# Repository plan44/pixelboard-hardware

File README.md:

# Pixelboard Hardware

The **Pixelboard** is a 80*40cm lounge table board only 24mm thick, integrating a 10x20 color pixel matrix, 8 touch keys, a linux controller with WiFi and ethernet and even a power supply. All disguised under a dark plexiglass, looking like a regular lounge table until touched...

With the current software (see [pixelboardd](https://github.com/plan44/pixelboardd) and [pixelboard-config in plan44-feed](https://github.com/plan44/plan44-feed/tree/for-lede-master/pixelboard-config)) you can play tetris (alone or 2 players each on one end of the board), watch Conway's game of life, let text messages scroll over the surface and display small 10x20 pixel PNG images (via web interface).

The board itself is made of 5 layers of lasered plywood and plexiglass. The construction plan is a [Affinity Designer](https://affinity.serif.com/en-us/designer/) drawing in `mechanics/` and there are SVG exports of the layers in `mechanics/exported SVGs for laser/`.

The pixels are made of 33mm spaced WS2813 LED strips, arranged in a 10*20 matrix, all power and data lines connected by two narrow PCBs (see KiCAD files in `electronics/connectorboard`, PCBs can be [ordered here](https://oshpark.com/shared_projects/2NEbDGZJ)). The board is designed such that it works for both sides of the matrix (flipped over at the far end).

The control board is built around a [Onion Omega2](https://onion.io/omega2/), a MediaTek MT7688 based MIPS board with built-in WiFi, 64MB RAM and 16MB Flash, running a LEDE/OpenWRT Linux based firmware (see [here](https://github.com/plan44/plan44-feed/blob/for-lede-master/pixelboard-config/README.md) for how to build the firmware from scratch). The KiCAD files are in `electronics/controlboard`, PCBs can be [ordered here](https://oshpark.com/shared_projects/cvgoJ8vJ)).

The two identical touch key boards are based on the AT42QT1070 chip for handling the touch detection plus a i2c port extender for connecting the indicator LEDs placed in the middle under each touch key. The KiCAD files are in `electronics/touchboard`, PCBs can be [ordered here](https://oshpark.com/shared_projects/GfQ63cgI)).

And in `photos` there are a few images showing various states of assembling all this:

Front glass removed

Controlboard side, just base plate and first lasered frame (lower carrier) keeping the LED matrix, cables, and controlboard in place.

Power supply side, base plate and lower carrier.

Power supply side, now with all plywood layers and touchboard mounted.

Controlboard side, all plywood layers mounted, diffusor plexi sqares inserted, touchboard mounted. Note that this photo does not yet show the hole for a little speaker connected to the MAX98357A i2s amp (but the plan drawings have it).

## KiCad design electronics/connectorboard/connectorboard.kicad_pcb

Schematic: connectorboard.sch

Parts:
C1, C2, C3, C4: 100nF; C_Rect_L7_W2.5_P5
CN1, CN3, CN5, CN7, CN9, CN12, CN14, CN16, CN18, CN20: WS2813-CONN-IN; plan44-WS2813-CONN
CN2, CN4, CN6, CN8, CN10, CN11, CN13, CN15, CN17, CN19: WS2813-CONN-OUT; plan44-WS2813-CONN
J1: STELVIO-2P-508; plan44-STELVIO-2P-508
P1: CONN_01X04; Pin_Header_Straight_1x04

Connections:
+5V: C1.1, C2.1, C3.1, C4.1, CN1.1 (+5V), CN2.4, CN3.1 (+5V), CN4.4, CN5.1 (+5V), CN6.4, CN7.1 (+5V), CN8.4, CN9.1 (+5V), CN10.4, CN11.4, CN12.1 (+5V), CN13.4, CN14.1 (+5V), CN15.4, CN16.1 (+5V), CN17.4, CN18.1 (+5V), CN19.4, CN20.1 (+5V), J1.2, P1.4
GND: C1.2, C2.2, C3.2, C4.2, CN1.4 (GND), CN2.1, CN3.4 (GND), CN4.1, CN5.4 (GND), CN6.1, CN7.4 (GND), CN8.1, CN9.4 (GND), CN10.1, CN11.1, CN12.4 (GND), CN13.1, CN14.4 (GND), CN15.1, CN16.4 (GND), CN17.1, CN18.4 (GND), CN19.1, CN20.4 (GND), J1.1, P1.1, P1.3
unnamed: CN1.2 (DI), P1.2
unnamed: CN2.2, CN3.3 (BI)
unnamed: CN2.3, CN3.2 (DI)
unnamed: CN4.2, CN5.3 (BI)
unnamed: CN4.3, CN5.2 (DI)
unnamed: CN6.2, CN7.3 (BI)
unnamed: CN6.3, CN7.2 (DI)
unnamed: CN8.2, CN9.3 (BI)
unnamed: CN8.3, CN9.2 (DI)
unnamed: CN11.2, CN12.3 (BI)
unnamed: CN11.3, CN12.2 (DI)
unnamed: CN13.2, CN14.3 (BI)
unnamed: CN13.3, CN14.2 (DI)
unnamed: CN15.2, CN16.3 (BI)
unnamed: CN15.3, CN16.2 (DI)
unnamed: CN17.2, CN18.3 (BI)
unnamed: CN17.3, CN18.2 (DI)
unnamed: CN19.2, CN20.3 (BI)
unnamed: CN19.3, CN20.2 (DI)

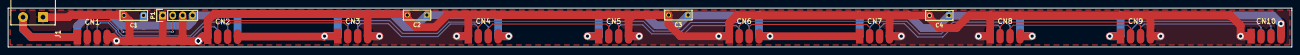
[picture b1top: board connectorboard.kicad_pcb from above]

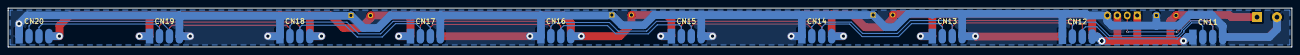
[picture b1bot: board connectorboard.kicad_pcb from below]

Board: 2 copper layers, 327.7 x 9.9 mm, 26 parts (10 on the bottom side), 21 nets.

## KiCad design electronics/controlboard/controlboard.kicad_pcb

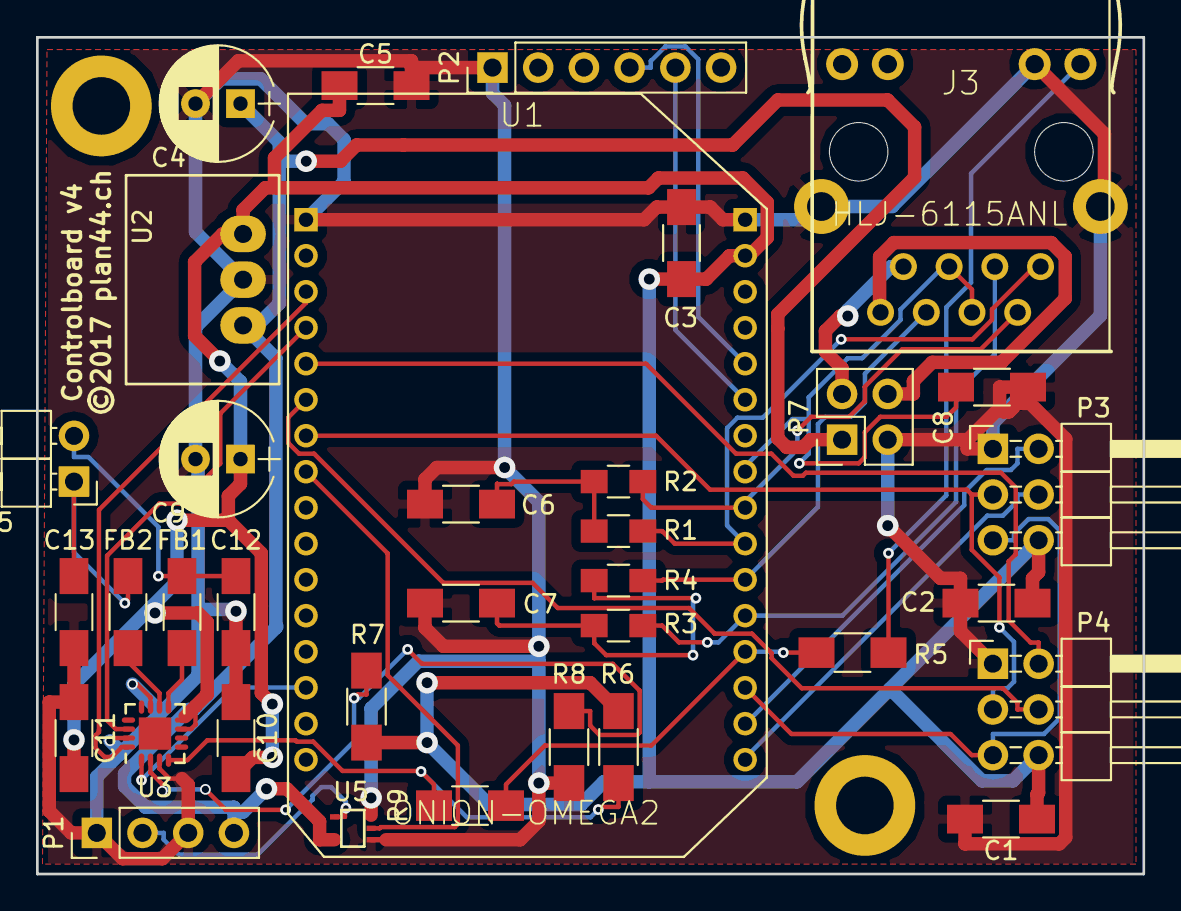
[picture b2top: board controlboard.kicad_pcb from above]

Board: 2 copper layers, 61.5 x 46.5 mm, 37 parts (0 on the bottom side), 33 nets.

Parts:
C1, C2, C3, C5, C6, C7, C11: 100nF; C_1206_HandSoldering
C4: 10uF; CP_Radial_D6.3mm_P2.50mm
C8: 1uF; C_1206_HandSoldering
C9: 33uF; CP_Radial_D6.3mm_P2.50mm
C10: 10uF; C_1206_HandSoldering
C12, C13: 220pF; C_1206_HandSoldering
FB1, FB2: Ferritebead; C_1206_HandSoldering
J3: HLJ-6115ANL; plan44-HLJ-6115ANL
MH1, MH2: CONN_01X01; MountingHole_3.2mm_M3_DIN965_Pad
P1: CONN_01X04; Pin_Header_Straight_1x04_Pitch2.54mm
P2: FDI_Cable; Pin_Header_Straight_1x06_Pitch2.54mm
P3, P4: CONN_02X03; Pin_Header_Angled_2x03_Pitch2.54mm
P5: CONN_01X02; Pin_Header_Angled_1x02_Pitch2.54mm
P7: CONN_02X02; Pin_Header_Straight_2x02_Pitch2.54mm
R1, R2, R3, R4: 49.9_1%; R_0805_HandSoldering
R5: 1k; R_1206_HandSoldering
R6, R9: 1M; R_1206_HandSoldering
R7, R8: 100k; R_1206_HandSoldering
U1: ONION-OMEGA2; plan44-ONION-2MM-2X16
U2: Recom_R78Cxx; plan44-Recom-R78Cxx
U3: MAX98357A; QFN-16-1EP_3x3mm_Pitch0.5mm
U5: 74AHCT1G125; SOT-353

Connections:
+3V3: C1.1, C2.1, C3.1, C5.1, C9.1, C10.1, C11.1, P3.6, P4.6, R6.1, R7.1, U1.B2, U2.3, U3.7, U3.8
+5V: C4.1, P1.4, P7.1, U2.1, U5.5
/BITCLK: U1.A3, U3.16
/ETHLED_AMPEN: R5.1, R9.1, U1.B13
/ETH_NETPWR: C8.1, J3.4, J3.5, U1.B8
/ETH_PWR+: J3.7, P7.2
/ETH_PWR-: J3.8, P7.4
/ETH_RX+: J3.3, R3.2, U1.B12
/ETH_RX-: J3.6, R4.2, U1.B11
/ETH_TX+: J3.1, R1.2, U1.B10
/ETH_TX-: J3.2, R2.2, U1.B9
/I2C_SCL_1: P3.2, U1.B15
/I2C_SCL_2: P4.2, U1.A5
/I2C_SDA_1: P3.4, U1.B16
/I2C_SDA_2: P4.4, U1.A6
/I2S_DOUT: U1.A14, U3.1
/LEDCHAIN_DATA_3V: U1.A8, U5.2
/LEDCHAIN_DATA_5V: P1.2, U5.4
/LRCLK_WS: U1.A4, U3.14
/Omega_RX: P2.4, U1.B5
/Omega_TX: P2.5, U1.B6
/SD_MODE: R6.2, R9.2, U3.4
/TOUCH_CHG: P3.5, P4.5, U1.B14
/TOUCH_RST: P3.3, P4.3, U1.A7
GND: C1.2, C2.2, C3.2, C4.2, C5.2, C6.2, C7.2, C8.2, C9.2, C10.2, C11.2, C12.2, C13.2, J3.10, J3.S1, J3.S2, P1.1, P1.3, P2.1, P3.1, P4.1, P7.3, R8.1, U1.A1, U1.B1, U2.2, U3.3, U3.11, U3.15, U5.1, U5.3
unnamed: C6.1, R1.1, R2.1
unnamed: C7.1, R3.1, R4.1
unnamed: C12.1, FB1.2, P5.2
unnamed: C13.1, FB2.2, P5.1
unnamed: FB1.1, U3.9
unnamed: FB2.1, U3.10
unnamed: J3.9, R5.2
unnamed: R7.2, R8.2, U3.2

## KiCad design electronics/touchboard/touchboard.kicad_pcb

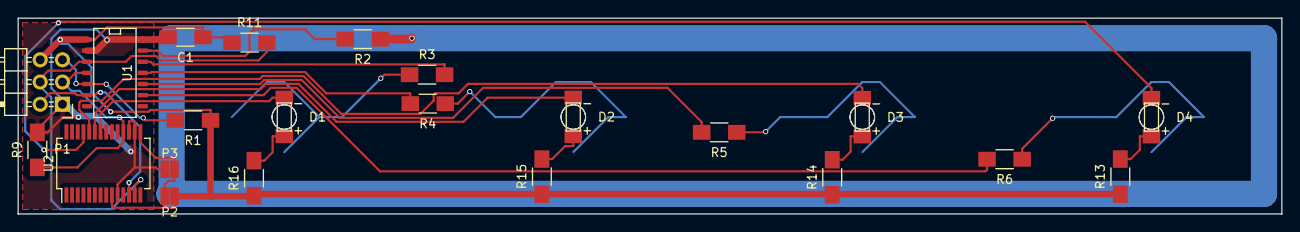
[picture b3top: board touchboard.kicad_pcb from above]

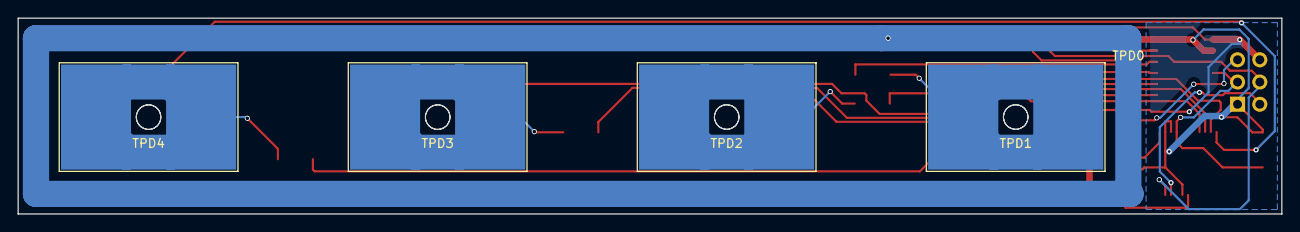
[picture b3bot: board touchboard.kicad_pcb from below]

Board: 2 copper layers, 144.3 x 22.4 mm, 27 parts (5 on the bottom side), 25 nets.

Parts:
C1: C; C_1206_HandSoldering
D1, D2, D3, D4: Led_Small; LED1206_rev_mount
P1: CONN_02X03; Pin_Header_Angled_2x03
P2, P3: CONN_01X02; CONFIG-PAD-2P
R1, R3, R4, R5, R6, R11: 4.7k; R_1206_HandSoldering
R2: 4.7k-20k; R_1206_HandSoldering
R9: 47k; R_1206_HandSoldering
R13, R14, R15, R16: 1.2k; R_1206_HandSoldering
TPD0: CONN_01X01; Measurement_Point_Round-SMD-Pad_Small
TPD1, TPD2, TPD3, TPD4: CONN_01X01; Touchpad_12x20_with_LED
U1: AT42QT1070; SOIC-14_N
U2: MCP23017; SSOP-28_5.3x10.2mm_Pitch0.65mm

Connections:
+3V3: C1.1, P1.6, P2.2, R1.1, R11.1, R13.1, R14.1, R15.1, R16.1, U1.1, U2.9
/GUARD: R2.1, TPD0.1
/I2C_SCL: P1.2, U1.6, U2.12
/I2C_SDA: P1.4, R11.2, U1.3, U2.13
/TOUCH1: R3.1, TPD1.1
/TOUCH2: R4.1, TPD2.1
/TOUCH3: R5.1, TPD3.1
/TOUCH4: R6.1, TPD4.1
/TOUCH_CHG: P1.5, R1.2, U1.5
/TOUCH_RST: P1.3, R9.1, U1.4, U2.18
GND: C1.2, P1.1, P3.2, R9.2, U1.2, U1.14, U2.10, U2.16, U2.17
unnamed: D1.1, U2.22
unnamed: D1.2, R16.2
unnamed: D2.1, U2.23
unnamed: D2.2, R15.2
unnamed: D3.1, U2.24
unnamed: D3.2, R14.2
unnamed: D4.1, U2.25
unnamed: D4.2, R13.2
unnamed: P2.1, P3.1, U2.15
unnamed: R2.2, U1.13
unnamed: R3.2, U1.12
unnamed: R4.2, U1.11
unnamed: R5.2, U1.10
unnamed: R6.2, U1.9

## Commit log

2017-09-02 Initial checkin, not complete yet
2017-09-02 KiCAD: correced library paths to reach the plan44-kicad library (when cloned from github into the same parent as pixelboard-hardware)
2017-09-02 Added PDFs of schematics
2017-09-02 Added README.md
2017-09-02 README.md + photos named such that they are displayed on github
2017-09-02 README.md - yet another photo name typo

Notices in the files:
electronics/controlboard/controlboard.kicad_pcb:
©2017 plan44.ch
